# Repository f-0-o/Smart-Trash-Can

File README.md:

# Smart-Trash-Can

#configuring git settings on Pi. Issue #43
#4:38

#4:28 pm 
#Congifuring pi to solve conflict markers

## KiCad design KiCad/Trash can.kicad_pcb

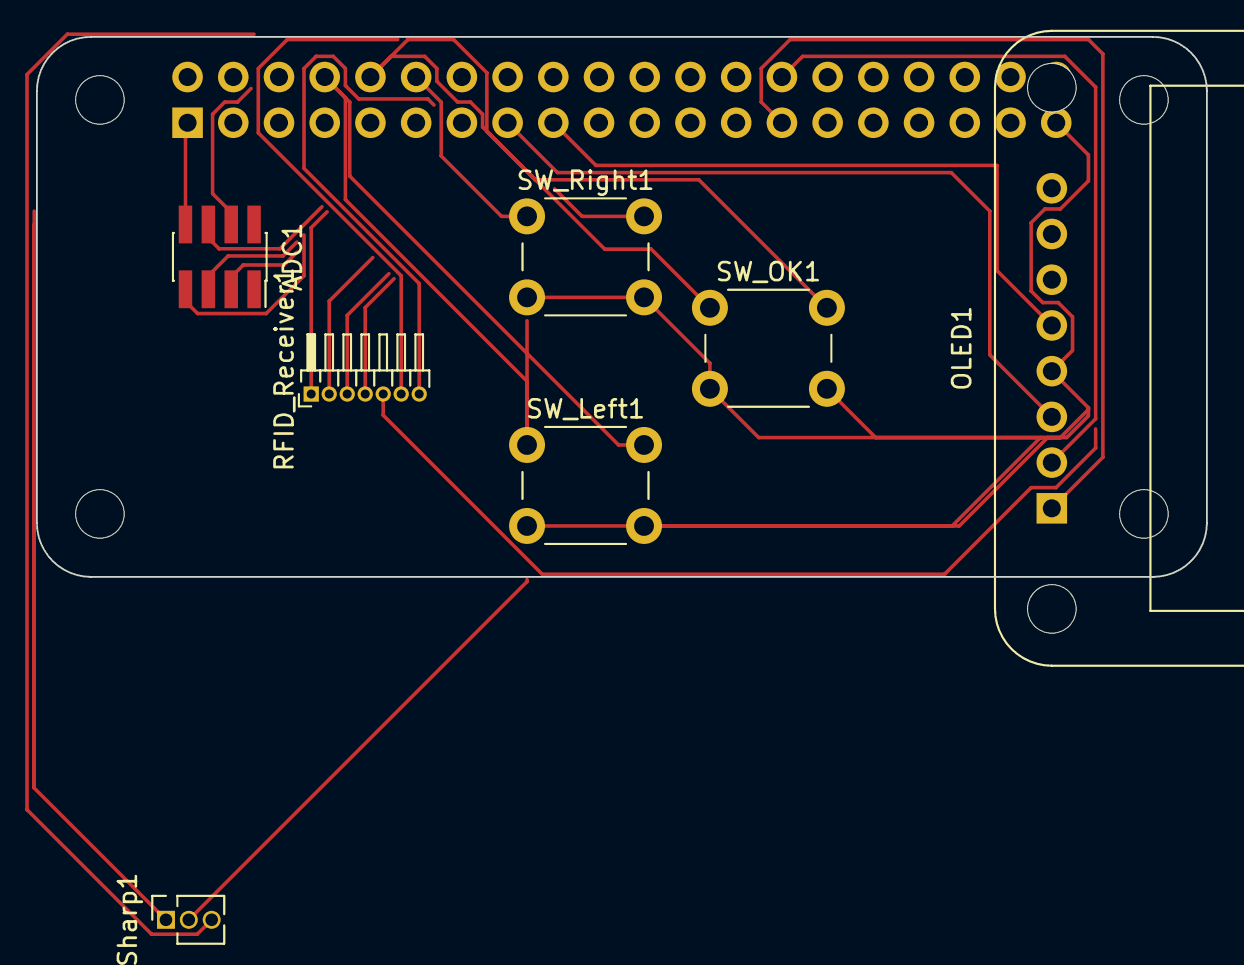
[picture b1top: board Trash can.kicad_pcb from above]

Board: 2 copper layers, 65.0 x 30.0 mm, 12 parts (1 on the bottom side), 19 nets.

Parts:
ADC1: MCP3002; PinSocket_2x04_P1.27mm_Vertical_SMD
J1: GPIO; PinSocket_2x20_P2.54mm_Vertical
MH1, MH2, MH3, MH4: MountingHole_2.7mm_M2.5
OLED1: SSD1306; Adafruit_SSD1306
RFID_Receiver1: RC5222; PinHeader_1x07_P1.00mm_Horizontal
SW_Left1: SW_Push; SW_PUSH_6mm_H5mm
SW_OK1: SW_Push; SW_PUSH_6mm_H5mm
SW_Right1: SW_Push; SW_PUSH_6mm
Sharp1: IR_DS; PinSocket_1x03_P1.27mm_Vertical

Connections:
+3V3: ADC1.8 (VDD/VREF), J1.1, J1.17, OLED1.5, Sharp1.1
+5V: J1.2, J1.4
/GPIO6: J1.31, RFID_Receiver1.3
/GPIO9/SPI0.MISO: ADC1.6 (DOUT), J1.21
/GPIO10/SPI0.MOSI: ADC1.5 (DIN), J1.19
/GPIO11/SPI0.SCLK: ADC1.7 (CLK), J1.23
/GPIO14/TXD0: J1.8, SW_Left1.1
/GPIO15/RXD0: J1.10, SW_OK1.1
/GPIO17: J1.11, RFID_Receiver1.1
/GPIO18/PCM.CLK: J1.12, SW_Right1.1
/GPIO19/PCM.FS: J1.35, RFID_Receiver1.5
/GPIO21/PCM.DOUT: J1.40, RFID_Receiver1.4
/GPIO22: J1.15, OLED1.3, RFID_Receiver1.2
/GPIO23: J1.16, RFID_Receiver1.6
/GPIO24: J1.18, RFID_Receiver1.7
/ID_SCL: J1.28, OLED1.2
/ID_SDA: J1.27, OLED1.1
GND: ADC1.3 (CH1), ADC1.4 (VSS), J1.6, J1.9, J1.14, J1.20, J1.25, J1.30, J1.34, J1.39, OLED1.4, SW_Left1.2, SW_OK1.2, SW_Right1.2, Sharp1.2
unnamed: ADC1.2 (CH0), Sharp1.3

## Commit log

2022-03-05 Create text_display
2022-03-05 Create image_display
2022-03-05 Create plot or chart display
2022-03-06 Create oled functions
2022-03-20 Trying to configure pi at 4:38
2022-03-20 display text on oled. issue #42
2022-04-06 Update plot or chart display
2022-04-18 KiCad
